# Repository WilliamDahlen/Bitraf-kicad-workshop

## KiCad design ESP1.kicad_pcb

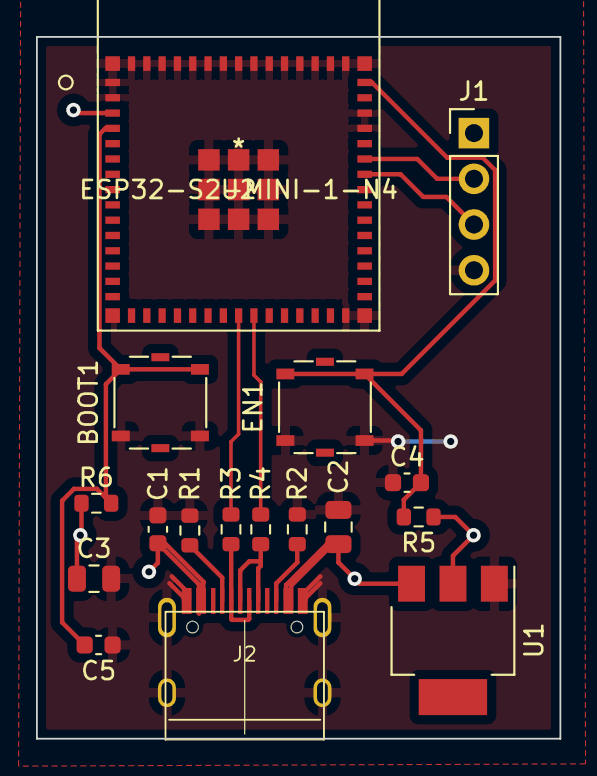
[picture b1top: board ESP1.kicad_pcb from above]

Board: 2 copper layers, 29.1 x 39.0 mm, 17 parts (0 on the bottom side), 13 nets.

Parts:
BOOT1: SW_Push; SW_SPST_Panasonic_EVQPL_3PL_5PL_PT_A08
C1, C4, C5: 0.1uF; C_0603_1608Metric
C2, C3: 10uF; C_0805_2012Metric
EN1: SW_Push; SW_SPST_Panasonic_EVQPL_3PL_5PL_PT_A08
J1: Conn_01x04_Male; PinHeader_1x04_P2.54mm_Vertical
J2: USB_C_Receptacle_USB2.0; TYPE-C-31-M-12
R1, R2: 5.1K; R_0603_1608Metric
R3, R4: 33R; R_0603_1608Metric
R5, R6: 10K; R_0603_1608Metric
U1: LM1117-3.3; SOT-223
U2: ESP32-S2-MINI-1-N4

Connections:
+3V3: C3.1, J1.1, R5.1, R6.1, U1.2 (VO), U2.3 (3V3)
+5V: C1.1, C2.1, J2.A4 (VBUS), J2.A9 (VBUS), J2.B4 (VBUS), J2.B9 (VBUS), U1.3 (VI)
/BOOT: BOOT1.2, C5.2, R6.2, U2.4 (IO0)
/ENABLE: C4.2, EN1.2, R5.2, U2.45 (EN)
GND: BOOT1.1, C1.2, C2.2, C3.2, C4.1, C5.1, EN1.1, J1.4, J2.A1 (GND), J2.A12 (GND), J2.B1 (GND), J2.B12 (GND), J2.S1 (SHIELD), R1.1, R2.1, U1.1 (GND), U2.1 (GND), U2.2 (GND), U2.30 (GND), U2.42 (GND), U2.43 (GND), U2.46 (GND), U2.47 (GND), U2.48 (GND), U2.49 (GND), U2.50 (GND), U2.51 (GND), U2.52 (GND), U2.53 (GND), U2.54 (GND), U2.55 (GND), U2.56 (GND), U2.57 (GND), U2.58 (GND), U2.59 (GND), U2.60 (GND), U2.61 (GND), U2.62 (GND), U2.63 (GND), U2.64 (GND), U2.65 (GND), U2.66 (GND), U2.67 (GND), U2.68 (GND), U2.69 (GND), U2.70 (GND), U2.71 (GND), U2.72 (GND), U2.73 (GND)
unnamed: J1.2, U2.40 (RXD0)
unnamed: J1.3, U2.39 (TXD0)
unnamed: J2.A5 (CC1), R1.2
unnamed: J2.A6 (D+), J2.B6 (D+), R4.2
unnamed: J2.A7 (D-), J2.B7 (D-), R3.2
unnamed: J2.B5 (CC2), R2.2
USB_N: R3.1, U2.23 (IO19)
USB_P: R4.1, U2.24 (IO20)

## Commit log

2022-03-26 Works for now
2022-05-04 Last few files before production

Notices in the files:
parts and their libraries:
Copyright 2021 Accelerated Designs. All rights reserved.
